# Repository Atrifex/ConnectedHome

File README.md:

# ConnectedHome
An IoT project.

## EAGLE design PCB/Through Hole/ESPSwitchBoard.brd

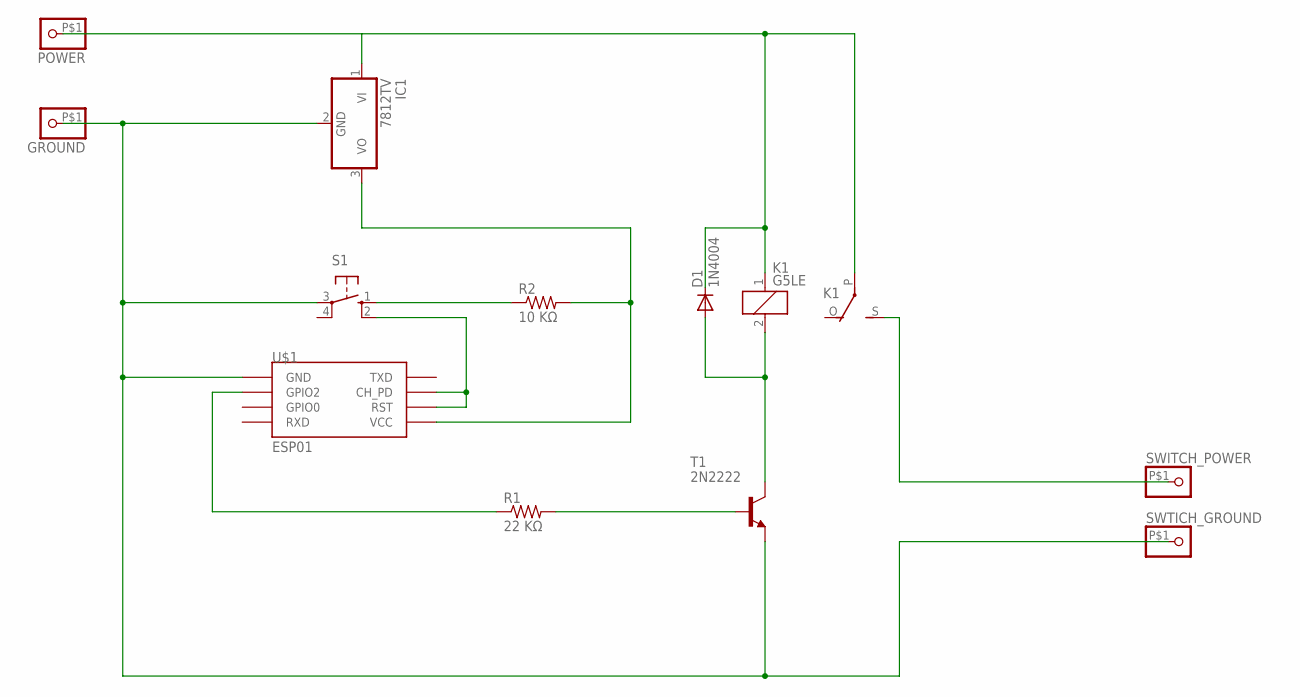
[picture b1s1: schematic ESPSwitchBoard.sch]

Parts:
D1: 1N4004; DO41-10
GROUND: PINHD-1X1-BIGPOGO; 1X1-BIGPOGO
IC1: 7812TV; TO220V
K1: G5LE
POWER: PINHD-1X1-BIGPOGO; 1X1-BIGPOGO
R1: 22 KΩ; 0805-THM
R2: 10 KΩ; 0805-THM
S1: 10-XX; B3F-10XX
SWITCH_POWER: PINHD-1X1-BIGPOGO; 1X1-BIGPOGO
SWTICH_GROUND: PINHD-1X1-BIGPOGO; 1X1-BIGPOGO
T1: 2N2222; TO92-EBC-OVAL
U$1: ESP01

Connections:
unnamed: D1.C, IC1.1 (VI), K1.1, K1.P, POWER.P$1
unnamed: GROUND.P$1, IC1.2 (GND), S1.3, SWTICH_GROUND.P$1, T1.E, U$1.GND
unnamed: IC1.3 (VO), R2.2, U$1.VCC
unnamed: K1.S, SWITCH_POWER.P$1
unnamed: D1.A, K1.2, T1.C
unnamed: R1.2, T1.B
unnamed: R1.1, U$1.GPIO2
unnamed: R2.1, S1.1 (S)
unnamed: S1.2 (S1), U$1.CH_PD, U$1.RST

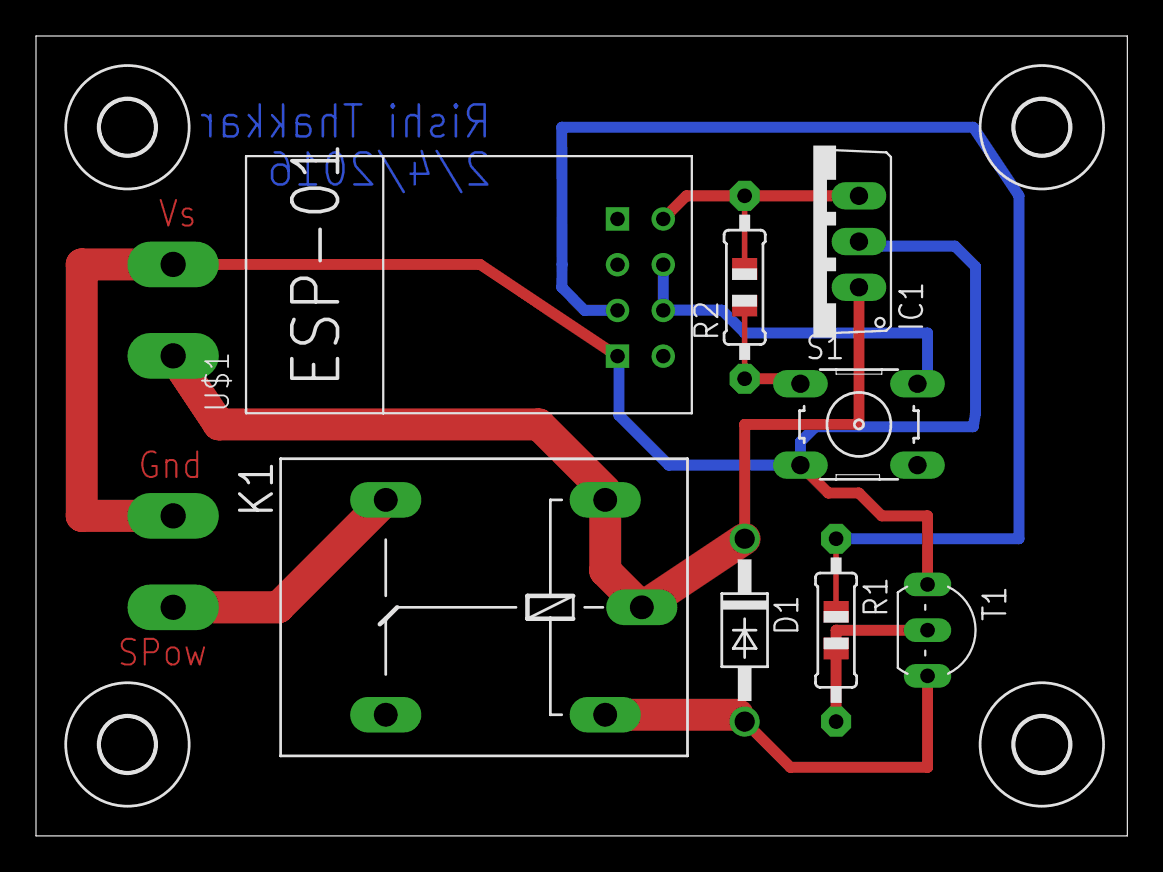
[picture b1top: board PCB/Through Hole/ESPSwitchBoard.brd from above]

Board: 2 copper layers, 60.6 x 44.4 mm, 16 parts (0 on the bottom side), 9 nets.

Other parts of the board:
U$2, U$3, U$4, U$5: 3,0

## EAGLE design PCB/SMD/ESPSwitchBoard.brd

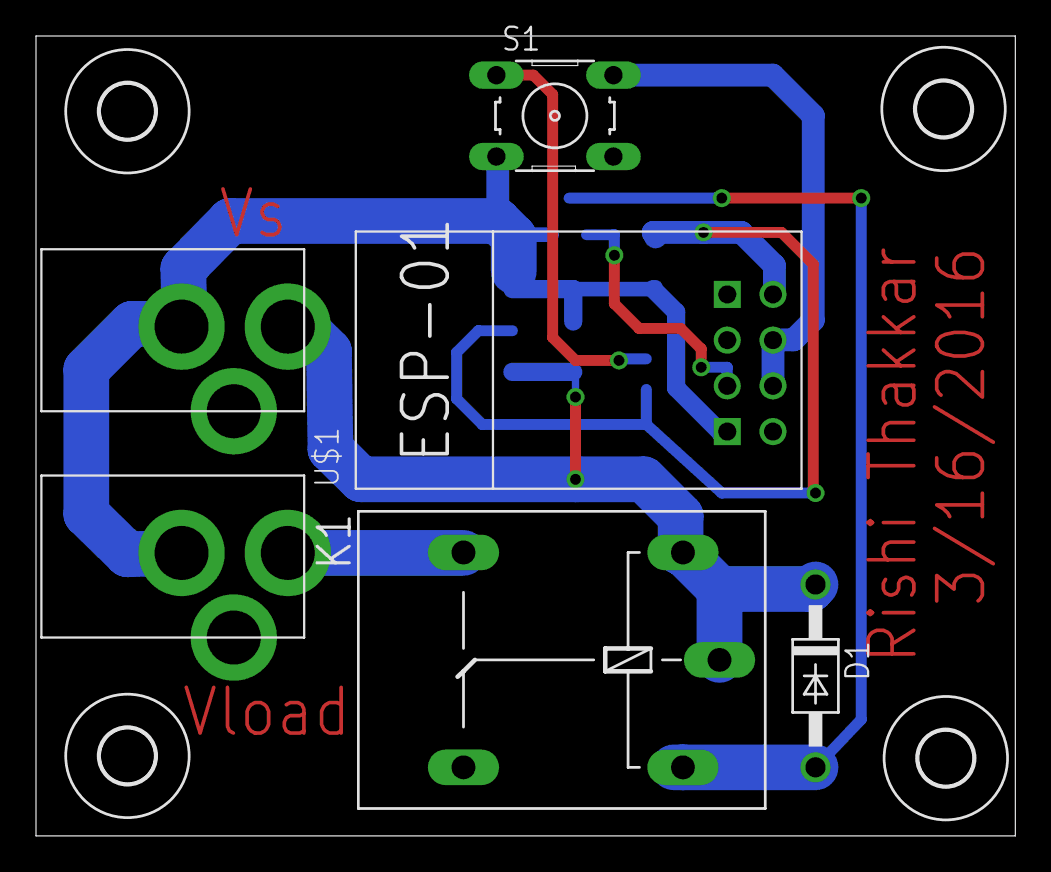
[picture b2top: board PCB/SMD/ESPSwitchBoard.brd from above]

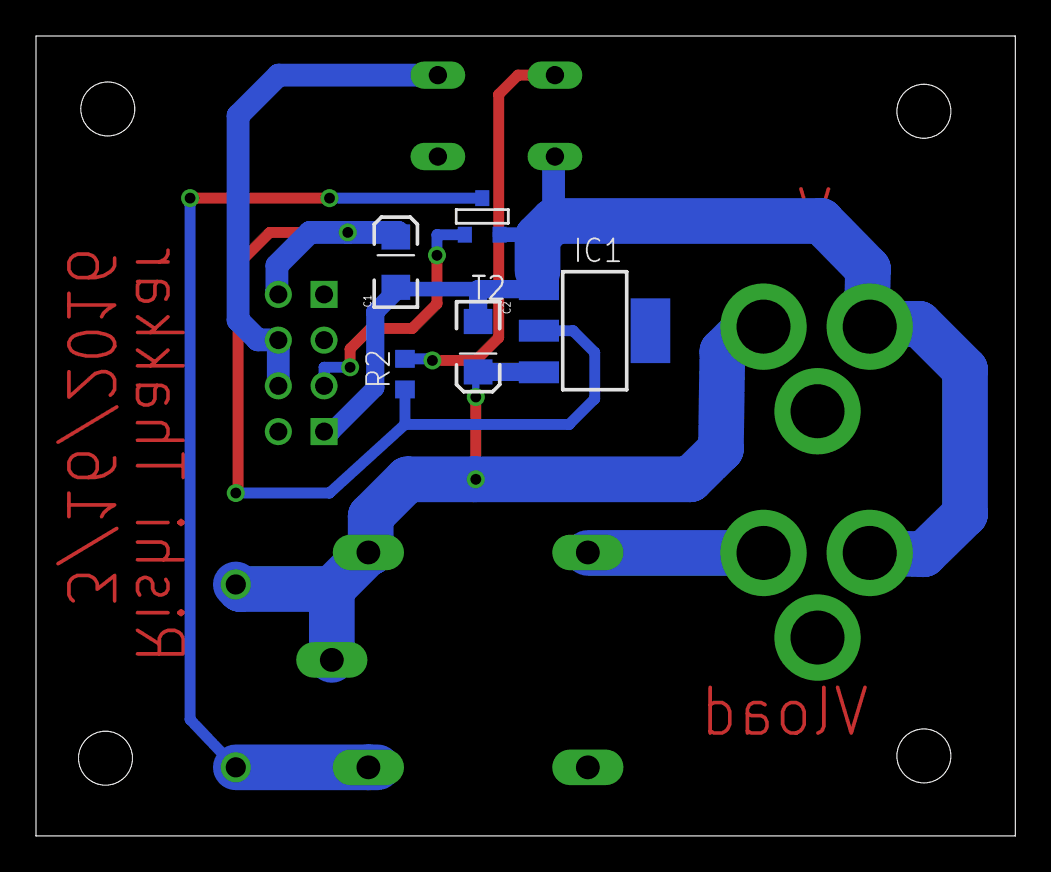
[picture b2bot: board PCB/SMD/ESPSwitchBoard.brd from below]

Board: 2 copper layers, 54.4 x 44.4 mm, 15 parts (5 on the bottom side), 8 nets.

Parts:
C1, C2: 10uF; EIA3216
D1: 1N4004; DO41-10
IC1: LM1117IMPX-3.3; SOT223
K1: G5LE
R2: 10 KΩ; R0603
S1: B3F-10XX
T2: SOT-23
U$1: ESP01
U$2, U$3, U$4, U$5: 3,0
V_LOAD: 2.1MMJACKTHM; PJ-102A
V_SOURCE: 2.1MMJACKTHM; PJ-102A

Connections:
unnamed: C2.A, D1.C, IC1.3, K1.1, K1.P, V_SOURCE.TIP
unnamed: C1.C, C2.C, IC1.1, S1.3, T2.2, U$1.GND, V_LOAD.RING, V_SOURCE.RING
unnamed: C1.A, IC1.2, R2.1, U$1.VCC
unnamed: K1.S, V_LOAD.TIP
unnamed: D1.A, K1.2, T2.1
unnamed: R2.2, S1.1
unnamed: T2.3, U$1.GPIO2
unnamed: S1.2, U$1.CH_PD, U$1.RST

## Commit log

2016-03-20 Project setup completed.
    Files have been organized and backups have been made for folders when
    needed.
2016-03-20 Reorganizing file structure.
2016-03-20 Restructuring directories.
2016-03-20 iOS App Started
    Decided to use a tabbed view template for the app. This will allow for
    best user interface.
2016-03-22 PCB files updated to the newest version.
2016-03-22 Folder restructuring.
2016-03-22 Started work on enduser script.
2016-04-22 edits made to documentation.
2016-04-22 HomeKit added.

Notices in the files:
parts and their libraries:
SparkFun-Retired: Licensing:Creative Commons ShareAlike 4.0 International - https://creativecommons.org/licenses/by-sa/4.0
